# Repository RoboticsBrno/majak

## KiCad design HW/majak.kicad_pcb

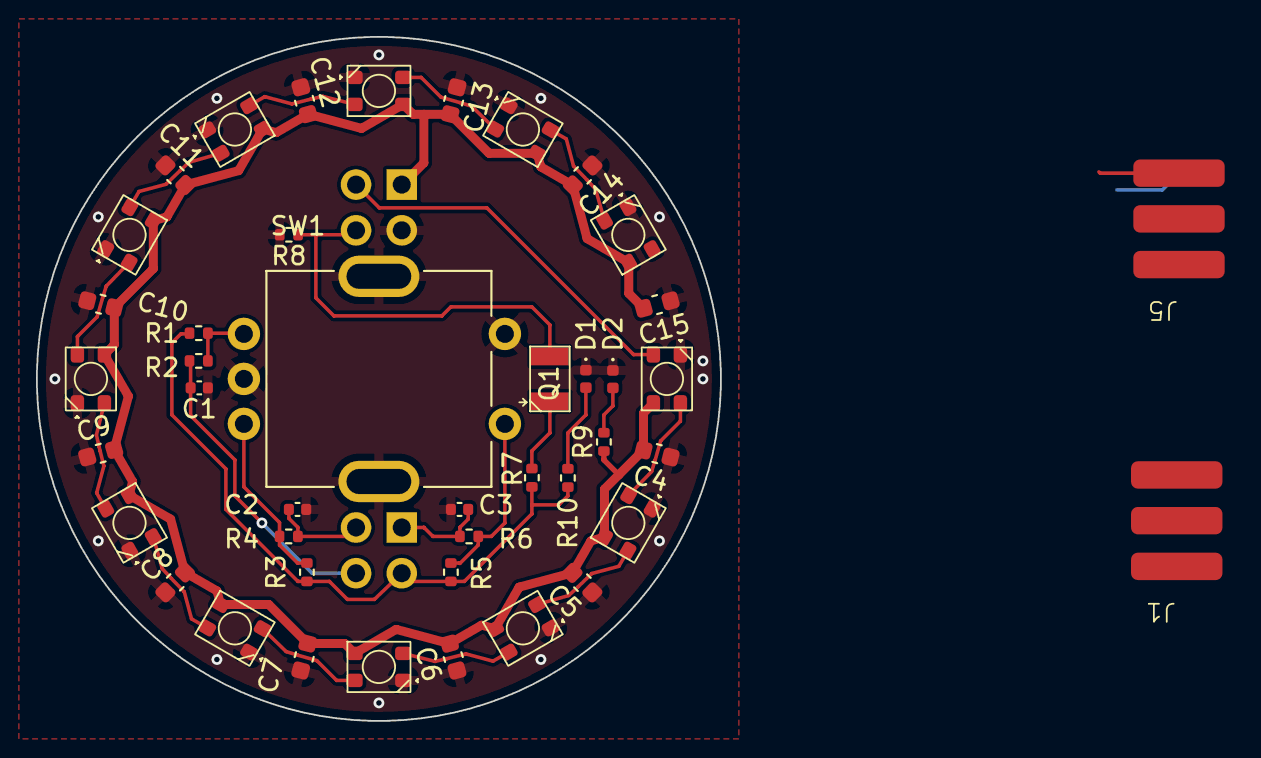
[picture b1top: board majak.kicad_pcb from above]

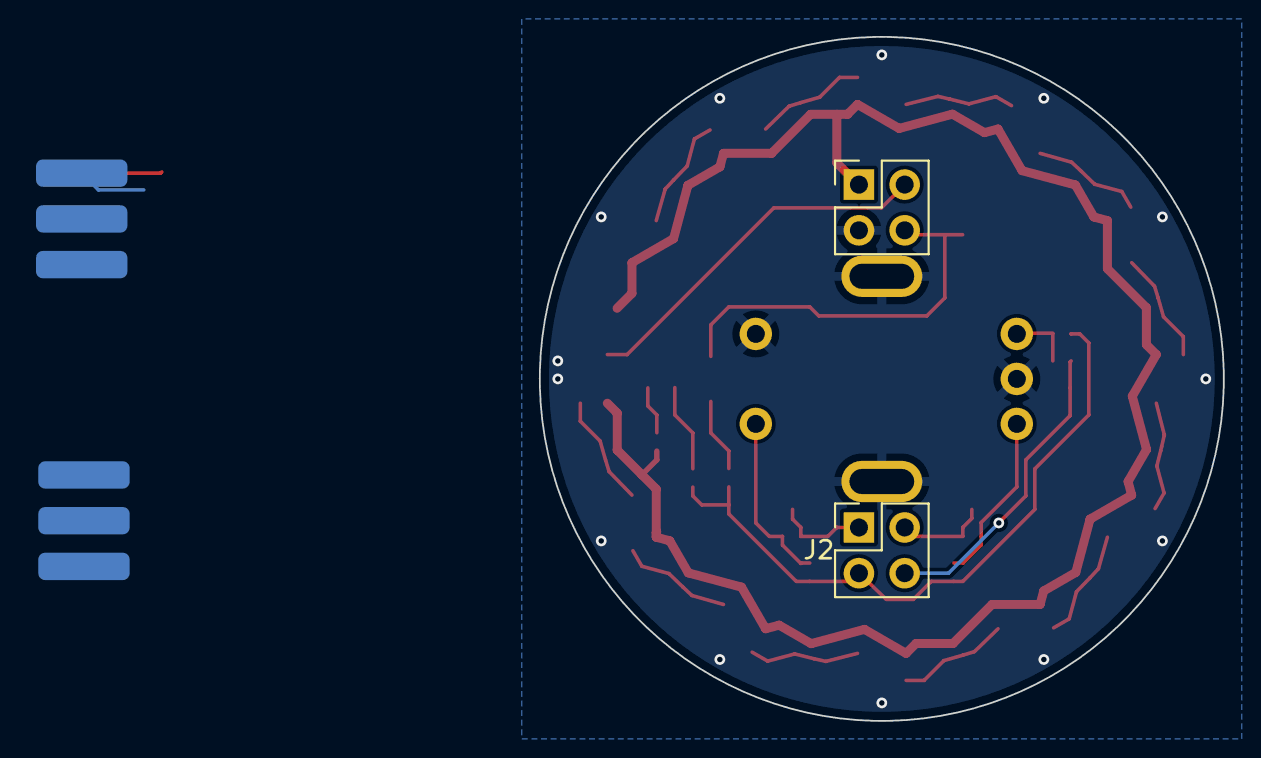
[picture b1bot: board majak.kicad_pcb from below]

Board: 2 copper layers, 38.0 x 38.0 mm, 45 parts (2 on the bottom side), 26 nets.

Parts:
C1, C2, C3: 10n; C_0402_1005Metric
C4, C5, C6, C7, C8, C9, C10, C11, C12, C13, C14, C15: 100n; C_0603_1608Metric
D1, D2: LED; LED_0402_1005Metric
J1, J5: Conn_02x03_Odd_Even; SMD_PINHED_2x3
J2, J3: Conn_02x02_Odd_Even; PinHeader_2x02_P2.54mm_Vertical
LED1, LED2, LED3, LED4, LED5, LED6, LED7, LED8, LED9, LED10, LED11, LED12: WS2812B; 3528RGBW-WS2812B
Q1: Q_Photo_NPN; SMD,3.5x2.8x1.9mm
R1, R2, R3, R4, R5, R6, R8: 10k; R_0402_1005Metric
R7: 22k; R_0402_1005Metric
R9, R10: 1k; R_0402_1005Metric
SW1: RotaryEncoder_Switch; RotaryEncoder_Bourns_Vertical_PEC11H-4xxxF-Sxxxx

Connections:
/circle/3V3: J2.3, R1.1, R3.1, R5.2, R7.1, R10.1
/circle/5V: C4.2, C5.2, C6.2, C7.2, C8.2, C9.2, C10.2, C11.2, C12.2, C13.2, C14.2, C15.2, J3.1, LED1.3 (VDD), LED2.3 (VDD), LED3.3 (VDD), LED4.3 (VDD), LED5.3 (VDD), LED6.3 (VDD), LED7.3 (VDD), LED8.3 (VDD), LED9.3 (VDD), LED10.3 (VDD), LED11.3 (VDD), LED12.3 (VDD), R9.1
/circle/ENC_A: C1.2, J2.4, R2.1
/circle/ENC_B: C2.2, J2.2, R4.1
/circle/GND: C1.1, C2.1, C3.2, C4.1, C5.1, C6.1, C7.1, C8.1, C9.1, C10.1, C11.1, C12.1, C13.1, C14.1, C15.1, D1.1 (K), D2.1 (K), J3.3, LED1.1 (GND), LED2.1 (GND), LED3.1 (GND), LED4.1 (GND), LED5.1 (GND), LED6.1 (GND), LED7.1 (GND), LED8.1 (GND), LED9.1 (GND), LED10.1 (GND), LED11.1 (GND), LED12.1 (GND), R8.2, SW1.C, SW1.S1, SW1.SH1, SW1.SH2
/circle/LEDS: J3.2, LED1.2 (DIN)
/circle/SENZOR_SVETLA: J3.4, Q1.2 (E), R8.1
/circle/SWITCH: C3.1, J2.1, R6.2
/mainboard/GND: J1.5, J1.6, J5.1, J5.2, J5.3
unnamed: D1.2 (A), R10.2
unnamed: D2.2 (A), R9.2
unnamed: LED1.4 (DOUT), LED2.2 (DIN)
unnamed: LED2.4 (DOUT), LED3.2 (DIN)
unnamed: LED3.4 (DOUT), LED4.2 (DIN)
unnamed: LED4.4 (DOUT), LED5.2 (DIN)
unnamed: LED5.4 (DOUT), LED6.2 (DIN)
unnamed: LED6.4 (DOUT), LED7.2 (DIN)
unnamed: LED7.4 (DOUT), LED8.2 (DIN)
unnamed: LED8.4 (DOUT), LED9.2 (DIN)
unnamed: LED9.4 (DOUT), LED10.2 (DIN)
unnamed: LED10.4 (DOUT), LED11.2 (DIN)
unnamed: LED11.4 (DOUT), LED12.2 (DIN)
unnamed: Q1.1 (C), R7.2
unnamed: R1.2, R2.2, SW1.A
unnamed: R3.2, R4.2, SW1.B
unnamed: R5.1, R6.1, SW1.S2

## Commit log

2024-04-25 Add KiCad locks (*.lck) to .gitignore
